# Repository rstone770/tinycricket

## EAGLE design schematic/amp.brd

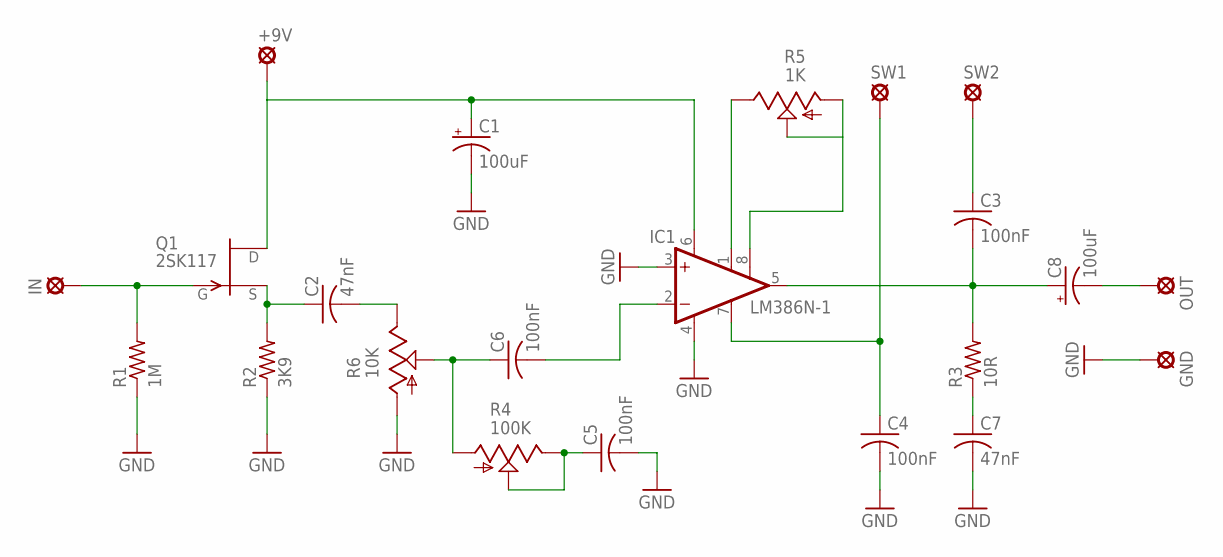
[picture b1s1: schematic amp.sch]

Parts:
+9V: MCS10B
C1, C8: 100uF; TT2D5
C2, C7: 47nF; C050-025X075
C3, C4, C5, C6: 100nF; C050-025X075
GND: MCS10B
IC1: LM386N-1; DIL08
IN: MCS10B
OUT: MCS10B
Q1: 2SK117; TO-92
R1: 1M; 0207/7
R2: 3K9; 0207/7
R3: 10R; 0207/7
R4: 100K; B64Y
R5: 1K; B64Y
R6: 10K; B64Y
SW1, SW2: MCS10B

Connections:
GND: C1.-, C4.2, C5.2, C7.2, GND.MP, IC1.3 (+IN), IC1.4 (GND), R1.1, R2.1, R6.A
unnamed: IN.MP, Q1.2 (G), R1.2
unnamed: C2.1, Q1.3 (S), R2.2
unnamed: C2.2, R6.E
unnamed: C6.1, R4.A, R6.S
unnamed: C5.1, R4.E, R4.S
unnamed: C6.2, IC1.2 (-IN)
unnamed: +9V.MP, C1.+, IC1.6 (VS), Q1.1 (D)
unnamed: IC1.1 (GAIN), R5.E
unnamed: IC1.8 (GAIN), R5.A, R5.S
unnamed: C3.1, SW2.MP
unnamed: C4.1, IC1.7 (BYPASS), SW1.MP
unnamed: C7.1, R3.1
unnamed: C3.2, C8.+, IC1.5 (OUT), R3.2
unnamed: C8.-, OUT.MP

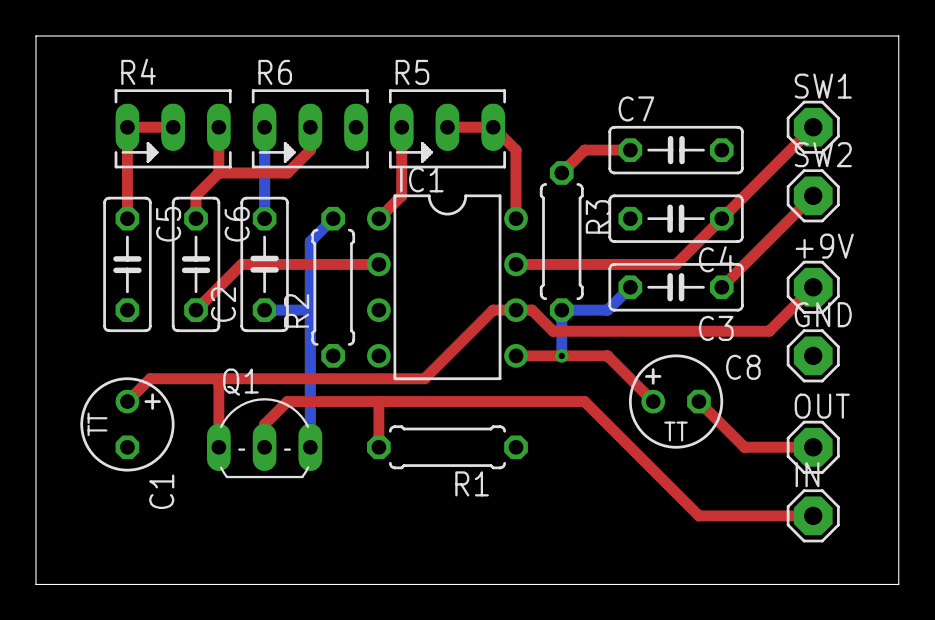
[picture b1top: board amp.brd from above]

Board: 2 copper layers, 47.9 x 30.5 mm, 22 parts (0 on the bottom side), 15 nets.

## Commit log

2017-06-24 :circus_tent: Added .gitattributes & .gitignore files
2017-06-24 Add 1590BB drill template.
2017-06-24 Fix pot drill size.
2017-06-24 Add layouts.
2017-06-25 Add pcb layouts.
2017-06-25 Remove stray via.
